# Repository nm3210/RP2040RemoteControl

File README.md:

# RP2040 RemoteControl

Collection of microcontroller projects to 'remote control' another device, including miscellaneous testing scripts.

These scripts are to be used within the CircuitPython framework, mostly using the RP2040 chipset. I will not be including any of the required libraries within this repo, however, they'll be linked/referenced where necessary. Most of the scripts will be prepended with `main_` to facilitate renaming them to -> `main.py` on the device's storage (I haven't figured out a better workflow yet).

## Main Projects

* [nRF24_RemoteControl](nRF24_RemoteControl): This contains the main scripts to setup boards to act as transmitter and receiver nodes of a basic remote control, sending commands from one to the other.

    This will potentially be used to control the modes of a string of lights by sending it different commands ("off", "on, white", etc.). The mechanism to select the mode may be via an accelerometer within a platonic solid (up = mode1, left side = mode3, etc).

    The receive module has been setup with an OshPark pcb to accept a Sparkfun Pro Micro with an rRF24L01 module on top of it.

    [ ](https://oshpark.com/shared_projects/c06FLb7A)

    The transmit module, however, is planned to be a [Sparkfun Thing Plus RP2040](https://www.sparkfun.com/products/17745) so that a battery can be used (the Thing Plus features a battery input and a handful of battery related circuits onboard).

## Testing & Prototyping Projects

* [MPU6050_Testing](MPU6050_Testing): Handful of scripts to test the MPU6050 accelerometer sensor

* [nRF24_Testing](nRF24_Testing): Scripts to test the nRF24L01 transceiver, mostly copied over from <https://github.com/2bndy5/CircuitPython_nRF24L01/tree/master/examples> after adjusting for the pins I have set up.

* [ColorDescriptors](https://github.com/nm3210/ColorDescriptors): Easily defined color descriptor words to be passed from one node to another

* [EasyStreamNrf24](https://github.com/nm3210/EasyStreamNrf24): Extends the normal NRF send/receive commands to combine multiple consecutive packets together

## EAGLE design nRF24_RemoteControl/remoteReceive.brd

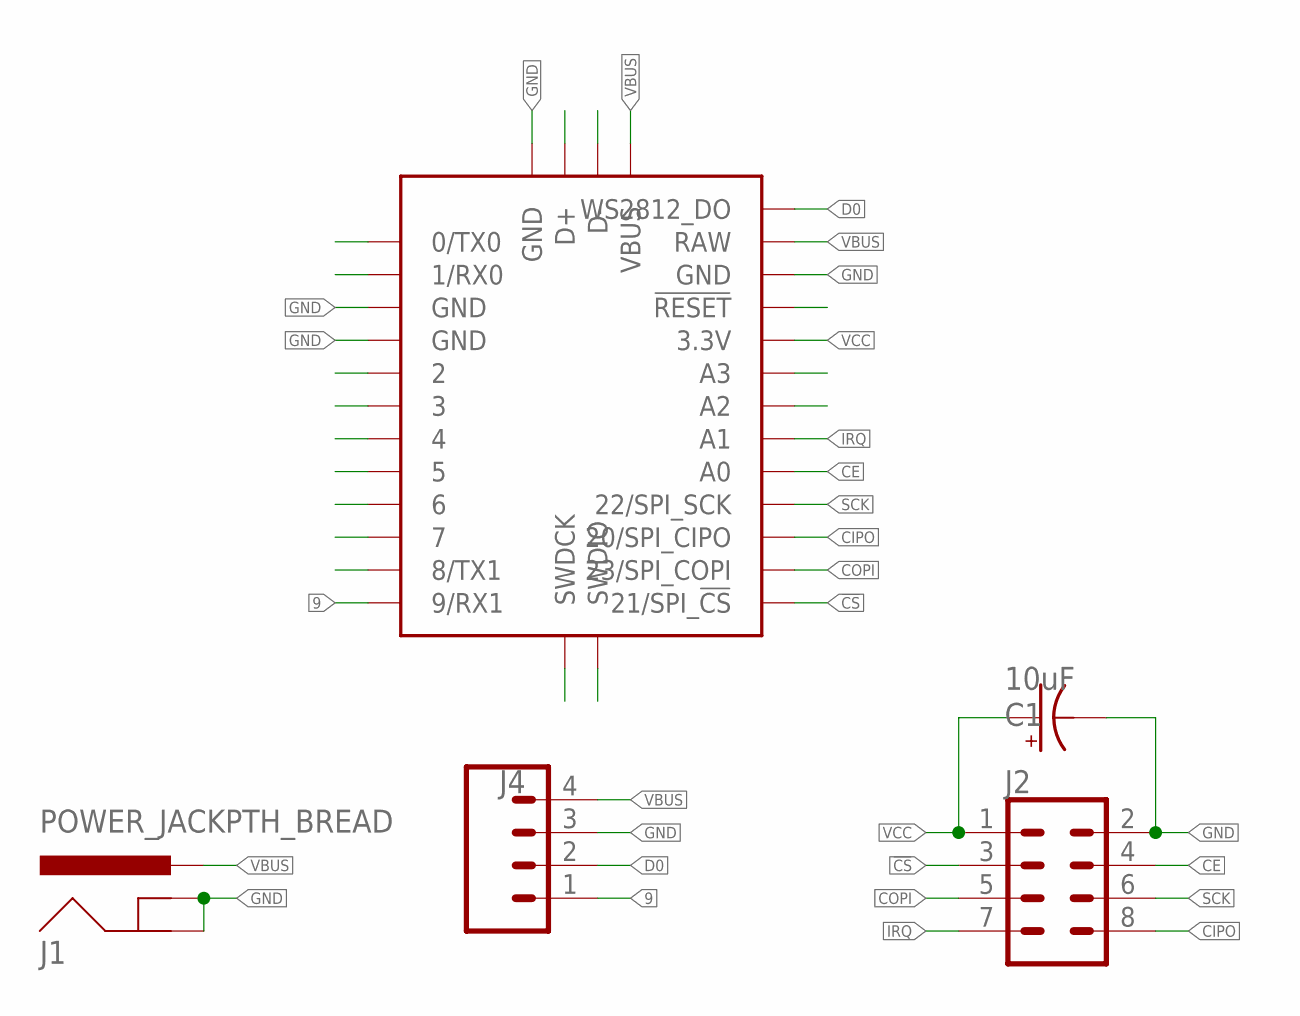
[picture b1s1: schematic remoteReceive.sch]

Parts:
C1: 10uF; CPOL-RADIAL-2.5MM-5MM-KIT
J1: POWER_JACKPTH_BREAD; POWER_JACK_PTH_BREAD
J2: CONN_04X2; 2X4
J4: CONN_04POLAR; MOLEX-1X4
U$1: SF17717_PROMICRORP2040_BREAKOUT

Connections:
9: J4.1, U$1.01L (9/RX1), U$1.01L_PADB (9/RX1), U$1.01L_PADT (9/RX1)
!CS: J2.3, U$1.12R (21/SPI_!CS), U$1.12R_PADB (21/SPI_!CS), U$1.12R_PADT (21/SPI_!CS)
CE: J2.4, U$1.08R (A0), U$1.08R_PADB (A0), U$1.08R_PADT (A0)
CIPO: J2.8, U$1.10R (20/SPI_CIPO), U$1.10R_PADB (20/SPI_CIPO), U$1.10R_PADT (20/SPI_CIPO)
COPI: J2.5, U$1.11R (23/SPI_COPI), U$1.11R_PADB (23/SPI_COPI), U$1.11R_PADT (23/SPI_COPI)
D0: J4.2, U$1.D0_B (WS2812_DO), U$1.D0_T (WS2812_DO)
GND: C1.2 (-), J1.GND, J1.GNDBREAK, J2.2, J4.3, U$1.02R (GND), U$1.02R_PADB (GND), U$1.02R_PADT (GND), U$1.09L (GND), U$1.09L_PADB (GND), U$1.09L_PADT (GND), U$1.10L (GND), U$1.10L_PADB (GND), U$1.10L_PADT (GND), U$1.GND_B (GND), U$1.GND_T (GND)
IRQ: J2.7, U$1.07R (A1), U$1.07R_PADB (A1), U$1.07R_PADT (A1)
unnamed: U$1.12L (0/TX0), U$1.12L_PADB (0/TX0), U$1.12L_PADT (0/TX0)
unnamed: U$1.11L (1/RX0), U$1.11L_PADB (1/RX0), U$1.11L_PADT (1/RX0)
unnamed: U$1.SWDCK_B (SWDCK), U$1.SWDCK_T (SWDCK)
unnamed: U$1.SWDIO_B (SWDIO), U$1.SWDIO_T (SWDIO)
unnamed: U$1.D+_B (D+), U$1.D+_T (D+)
unnamed: U$1.06L (4), U$1.06L_PADB (4), U$1.06L_PADT (4)
unnamed: U$1.05L (5), U$1.05L_PADB (5), U$1.05L_PADT (5)
unnamed: U$1.04L (6), U$1.04L_PADB (6), U$1.04L_PADT (6)
unnamed: U$1.03L (7), U$1.03L_PADB (7), U$1.03L_PADT (7)
unnamed: U$1.D-_B (D-), U$1.D-_T (D-)
unnamed: U$1.03R (!RESET), U$1.03R_PADB (!RESET), U$1.03R_PADT (!RESET)
unnamed: U$1.05R (A3), U$1.05R_PADB (A3), U$1.05R_PADT (A3)
unnamed: U$1.06R (A2), U$1.06R_PADB (A2), U$1.06R_PADT (A2)
unnamed: U$1.02L (8/TX1), U$1.02L_PADB (8/TX1), U$1.02L_PADT (8/TX1)
SCK: J2.6, U$1.09R (22/SPI_SCK), U$1.09R_PADB (22/SPI_SCK), U$1.09R_PADT (22/SPI_SCK)
SCL_1: U$1.08L (2), U$1.08L_PADB (2), U$1.08L_PADT (2)
SDA_1: U$1.07L (3), U$1.07L_PADB (3), U$1.07L_PADT (3)
VBUS: J1.PWR, J4.4, U$1.01R (RAW), U$1.01R_PADB (RAW), U$1.01R_PADT (RAW), U$1.VBUS_B (VBUS), U$1.VBUS_T (VBUS)
VCC: C1.1 (+), J2.1, U$1.04R (3.3V), U$1.04R_PADB (3.3V), U$1.04R_PADT (3.3V)

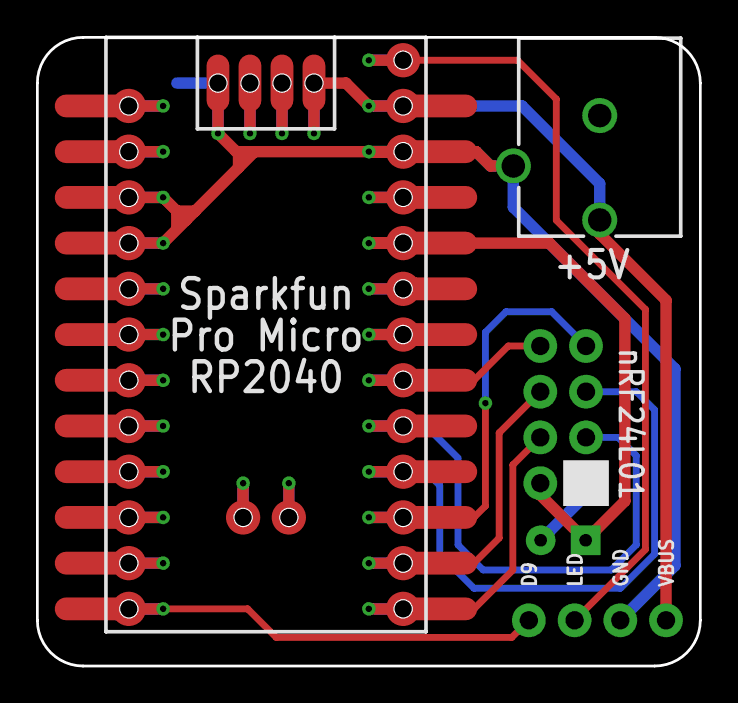
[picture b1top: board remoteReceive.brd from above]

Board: 2 copper layers, 36.8 x 34.9 mm, 5 parts (1 on the bottom side), 27 nets.

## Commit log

2021-04-17 Add testing scripts
2021-04-17 Add first attempt at sending/receiving data over the nRf25 modules
2021-04-18 Remove dead code that wasn't supposed to be left in!
2021-04-18 Minimize listen time to reduce power usage
    This involved using a multimeter (surprisingly my fluke didn't have \muamp on it) to measure the current going to the nRf24L01 module (through the adapter with 5v -> 3.3v).
    Nominal results went from about 17mA on full nrf.listen to about 3mA with the new timing within receivePayload (idle is about 2mA with the LED unsoldered for reference). I think this makes it less li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
2021-04-18 Add MPU6050 accel decoding on transmit module and send to receive side
    This sends the 'faceIdx' from the transmit module with the MPU6050 attached to the receive module where the LED changes color based on the orientation of the other module. The intention in the future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
2021-04-18 Bump up power output of transmit module to maximum
    The in-frequent transmit pulse timing still give quite a small average power usage (measured was around 3-5mA through a nRF24 adapter module with the LED unsoldered).
2021-04-22 Use consistent timers for all actions
    Instead of just relying on random sleeps, this checks against a timer to perform actions, which makes them slick and reliable.
2021-04-22 Only transmit the last valid face index, not zeros
2021-04-26 Add timer to receive to better control when and how long to listen
2021-04-26 Speed up detection of new orientation
2021-04-26 Add new EAGLE board/schematic for this project
    This combines a Sparkfun Pro Micro RP2040 with the nRF24L01 module in a nice little board with outputs for a WS2812 strip. This board was processed on OSH Park's website and can be found here: https: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
2021-06-13 Change receive pins to match the new oshpark pcb
2021-06-13 Add transmit code for Sparkfun Thing Plus board
2021-06-13 Add new EasyStream library for nRF24 transmission
2021-06-13 Update EasyStream reference
2021-06-13 Disable the IRQ line on the Sparkfun Thing Plus
    It was interferring with the I2C line below
2021-06-13 Change timers to use monotonic_ns instead
    I'm not entirely sure how things were being compared/computed with just the normal time.monotonic(), but changing to use the _ns resulted in much more accurate updates. Maybe there's some weird float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
2021-06-13 Disable debug prints by default
2021-06-13 Update some timing values
2021-06-13 Sync transmit code from SparkfunPlus to Sparkfun
2021-06-14 Use ColorDescriptor classes to handle color transmission and parsing
2021-06-14 Tweak the 'numAvgValues' to make it feel better
2021-06-21 Use updated ColorDescriptors to send color AND mode
2021-06-29 Update ColorDescriptors submodule
2021-10-11 Move update color out of detection check (allow update every loop)

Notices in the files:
parts and their libraries:
SparkFun-Connectors: Licensing: Creative Commons ShareAlike 4.0 International - https://creativecommons.org/licenses/by-sa/4.0
